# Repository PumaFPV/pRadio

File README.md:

# pRadio
PicoRadio, or PumaRadio, as you prefer...

A small VHF for paragliding. Configures via BLE with smartphone.
Since it has BLE connection to smartphone, could also be used as a remote to control XCtrack (move, zoom the map)
Mounts on the risers.
Aiming for 50g and ~10h of usage.

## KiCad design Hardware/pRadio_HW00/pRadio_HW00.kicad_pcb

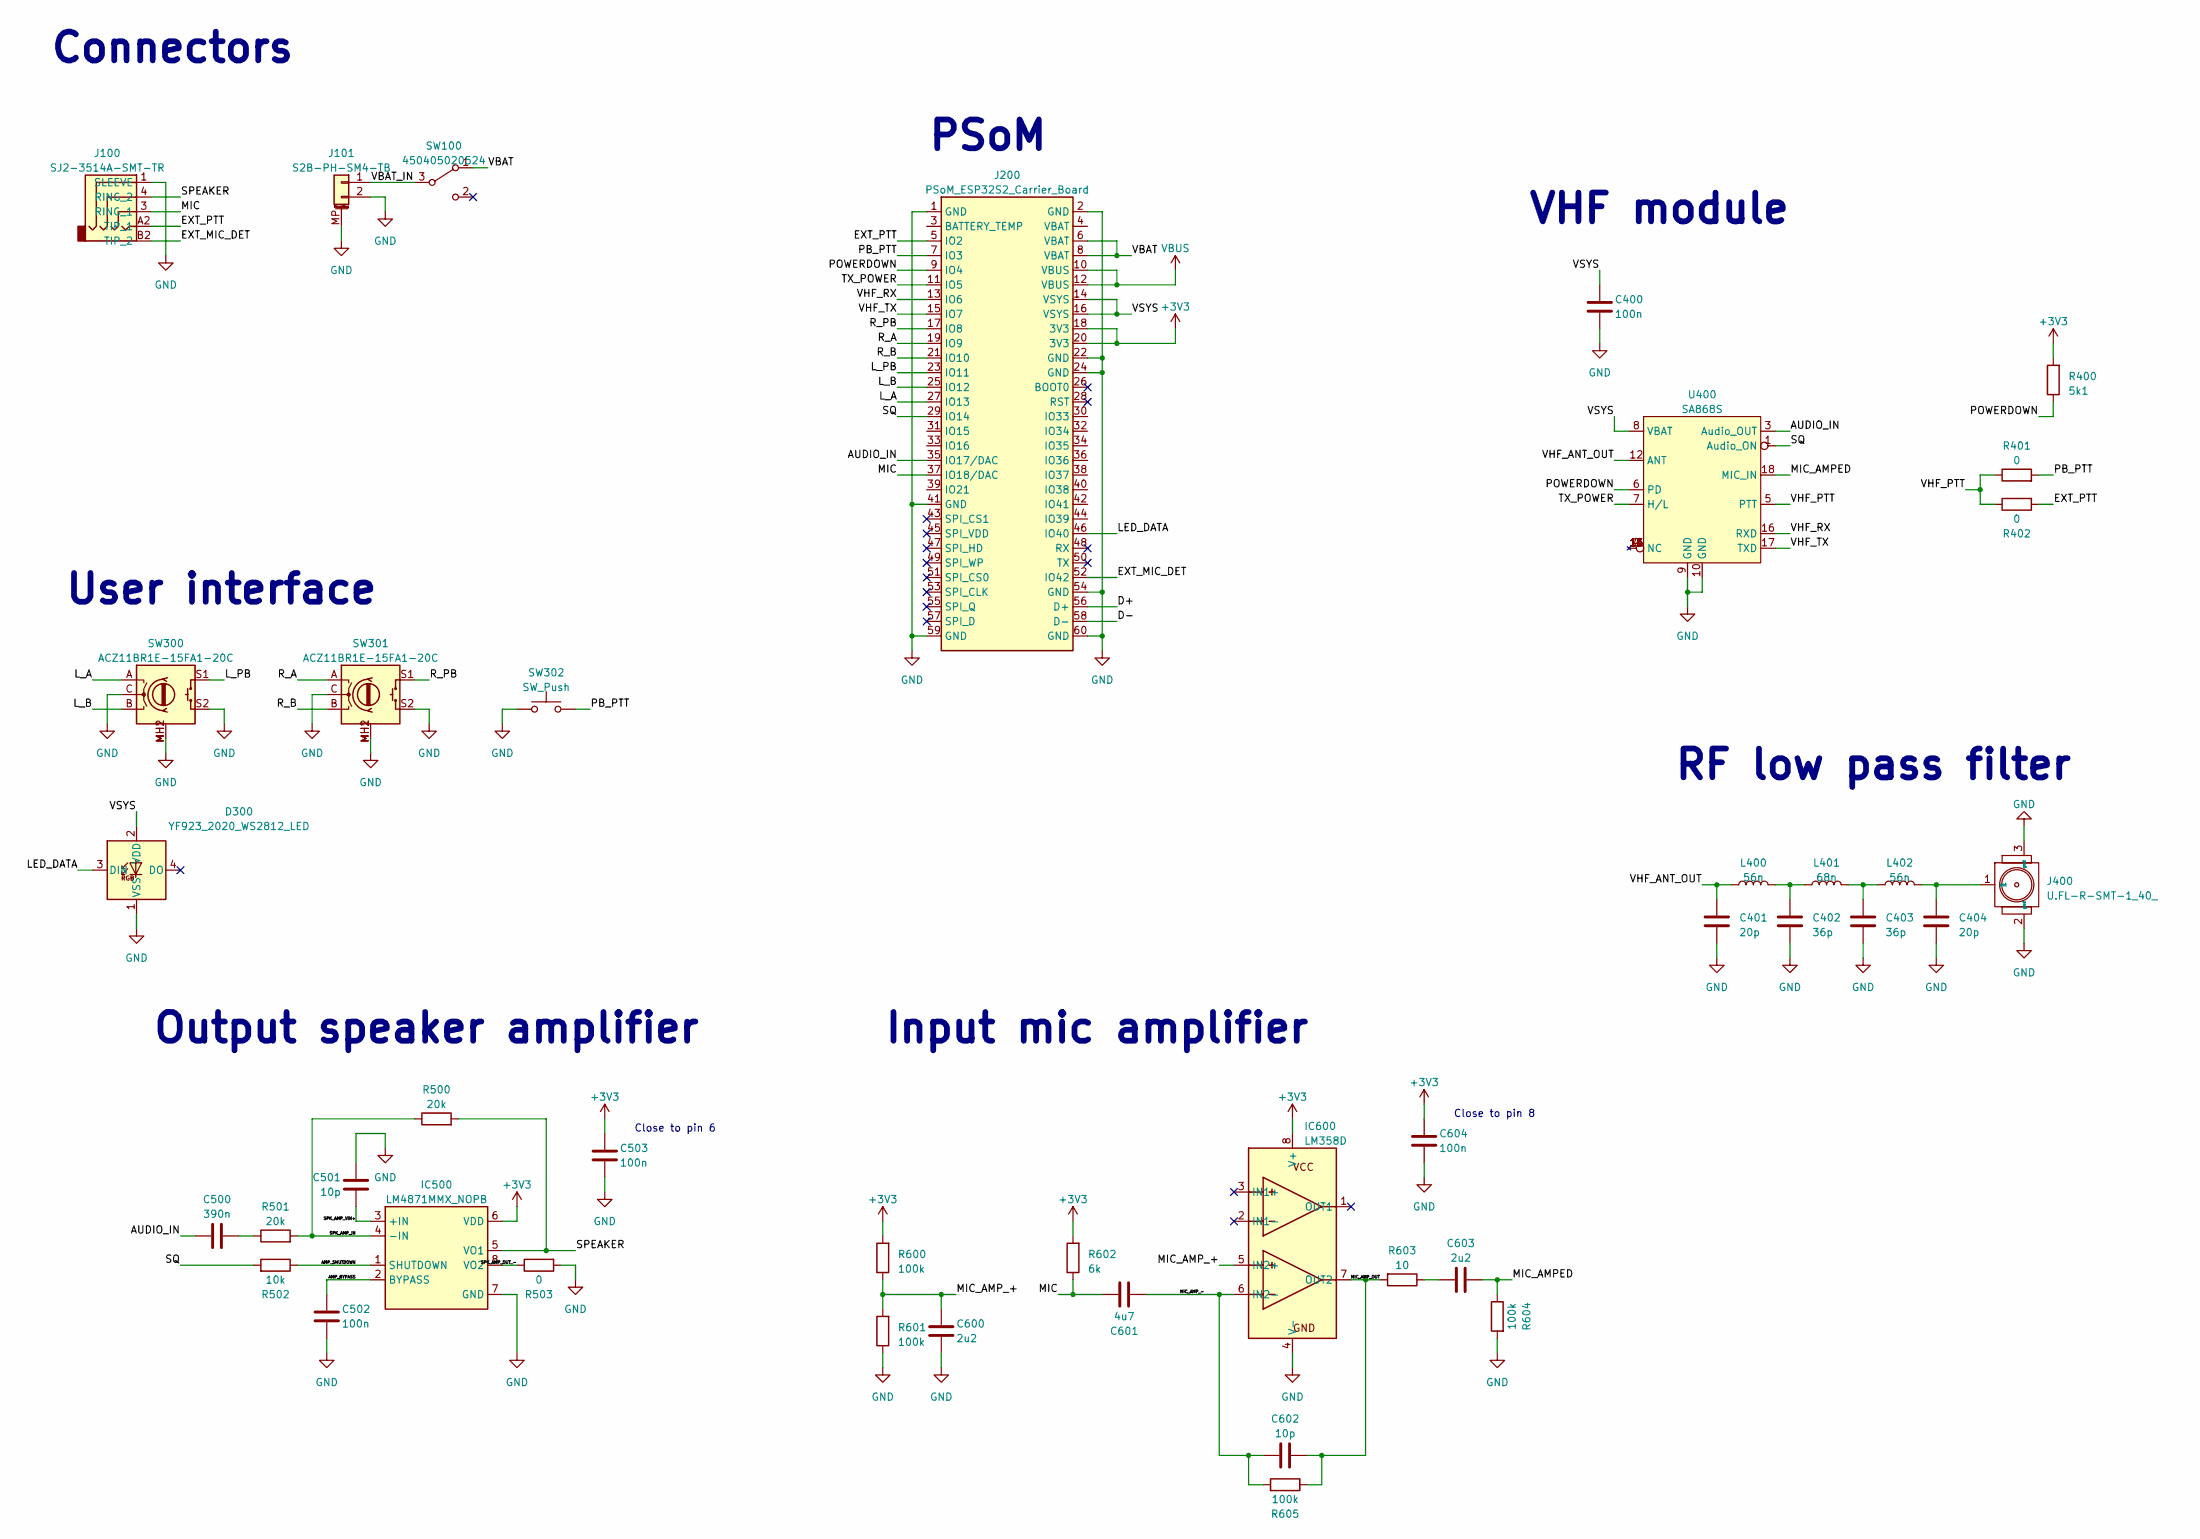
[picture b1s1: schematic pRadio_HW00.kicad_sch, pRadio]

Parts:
C400, C502, C503, C604: 100n; C_0402_1005Metric
C401, C404: 20p; C_0402_1005Metric
C402, C403: 36p; C_0402_1005Metric
C500: 390n; C_0603_1608Metric
C501, C602: 10p; C_0402_1005Metric
C600, C603: 2u2; C_0603_1608Metric
C601: 4u7; C_0603_1608Metric
D300: YF923_2020_WS2812_LED
IC500: LM4871MMX_NOPB; SOP65P490X110-8N; Mouser Part Number 926-LM4871MMX/NOPB
IC600: LM358D; SOIC127P600X175-8N; Mouser Part Number 511-LM358D
J100: SJ2-3514A-SMT-TR; SJ23514ASMTTR; Mouser Part Number 490-SJ2-3514A-SMT-TR
J101: S2B-PH-SM4-TB; JST_PH_S2B-PH-SM4-TB_1x02-1MP_P2.00mm_Horizontal
J200: PSoM_ESP32S2_Carrier_Board; PSoM_ESP32S2_00
J400: U.FL-R-SMT-1_40_; u.fl; Mouser Part Number 798-UFLRSMT140
L400, L402: 56n; L_0402_1005Metric
L401: 68n; L_0402_1005Metric
R400: 5k1; R_0201_0603Metric
R401, R402, R503: 0; R_0201_0603Metric
R500, R501: 20k; R_0201_0603Metric
R502: 10k; R_0201_0603Metric
R600, R601, R604, R605: 100k; R_0402_1005Metric
R602: 6k; R_0402_1005Metric
R603: 10; R_0402_1005Metric
SW100: 450405020524
SW300, SW301: ACZ11BR1E-15FA1-20C; ACZ11BR1E15FA120C
SW302: SW_Push; SW_Kailh_Choc_V1
U400: SA868S; RF818

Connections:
+3V3: C503.2, C604.2, IC500.6 (VDD), IC600.8 (V+), J200.18 (3V3), J200.20 (3V3), R400.2, R600.2, R602.2
/AMP_BYPASS: C502.2, IC500.2 (BYPASS)
/AMP_SHUTDOWN: IC500.1 (SHUTDOWN), R502.1
/AUDIO_IN: C500.1, J200.35 (IO17/DAC), U400.3 (Audio_OUT)
/D+: J200.56 (D+)
/D-: J200.58 (D-)
/EXT_MIC_DET: J100.B2 (TIP_2), J200.52 (IO42)
/EXT_PTT: J100.A2 (TIP_1), J200.5 (IO2), R402.2
/LED_DATA: D300.3 (DIN), J200.46 (IO40)
/L_A: J200.27 (IO13), SW300.A
/L_B: J200.25 (IO12), SW300.B
/L_PB: J200.23 (IO11), SW300.S1
/MIC: C601.1, J100.3 (RING_1), J200.37 (IO18/DAC), R602.1
/MIC_AMPED: C603.2, R604.1, U400.18 (MIC_IN)
/MIC_AMP_+: C600.2, IC600.5 (IN2+), R600.1, R601.2
/MIC_AMP_-: C601.2, C602.1, IC600.6 (IN2-), R605.2
/MIC_AMP_OUT: C602.2, IC600.7 (OUT2), R603.2, R605.1
/PB_PTT: J200.7 (IO3), R401.2, SW302.2
/POWERDOWN: J200.9 (IO4), R400.1, U400.6 (PD)
/R_A: J200.19 (IO9), SW301.A
/R_B: J200.21 (IO10), SW301.B
/R_PB: J200.17 (IO8), SW301.S1
/SPEAKER: IC500.5 (VO1), J100.4 (RING_2), R500.2
/SPK_AMP_IN: IC500.4 (-IN), R500.1, R501.2
/SPK_AMP_OUT_-: IC500.8 (VO2), R503.1
/SPK_AMP_VIN+: C501.1, IC500.3 (+IN)
/SQ: J200.29 (IO14), R502.2, U400.1 (Audio_ON)
/TX_POWER: J200.11 (IO5), U400.7 (H/L)
/VBAT: J200.6 (VBAT), J200.8 (VBAT), SW100.1 (A)
/VBAT_IN: J101.1, SW100.3 (B)
/VHF_ANT_OUT: C401.2, L400.1, U400.12 (ANT)
/VHF_PTT: R401.1, R402.1, U400.5 (PTT)
/VHF_RX: J200.13 (IO6), U400.16 (RXD)
/VHF_TX: J200.15 (IO7), U400.17 (TXD)
/VSYS: C400.2, D300.2 (VDD), J200.14 (VSYS), J200.16 (VSYS), U400.8 (VBAT)
GND: C400.1, C401.1, C402.1, C403.1, C404.1, C501.2, C502.1, C503.1, C600.1, C604.1, D300.1 (VSS), IC500.7 (GND), IC600.4 (V-), J100.1 (SLEEVE), J101.2, J101.MP (MountPin), J200.1 (GND), J200.2 (GND), J200.22 (GND), J200.24 (GND), J200.41 (GND), J200.54 (GND), J200.59 (GND), J200.60 (GND), J400.2 (gnd), J400.3 (gnd), R503.2, R601.1, R604.2, SW300.C, SW300.MH1, SW300.MH2, SW300.S2, SW301.C, SW301.MH1, SW301.MH2, SW301.S2, SW302.1, U400.9 (GND), U400.10 (GND)
unnamed: C402.2, L400.2, L401.1
unnamed: C403.2, L401.2, L402.1
unnamed: C500.2, R501.1
unnamed: C603.1, R603.1
unnamed: C404.2, J400.1 (ant), L402.2
VBUS: J200.10 (VBUS), J200.12 (VBUS)

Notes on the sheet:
User interface
Close to pin 6
PSoM
RF low pass filter
VHF module
Input mic amplifier
Output speaker amplifier
Close to pin 8
Connectors

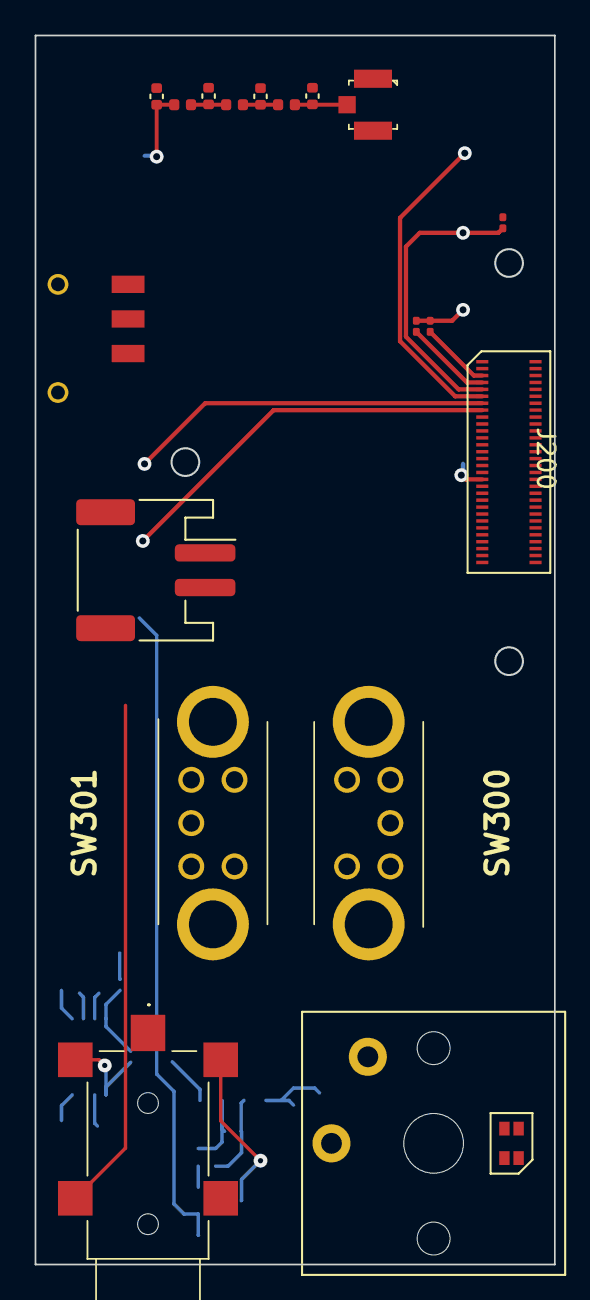
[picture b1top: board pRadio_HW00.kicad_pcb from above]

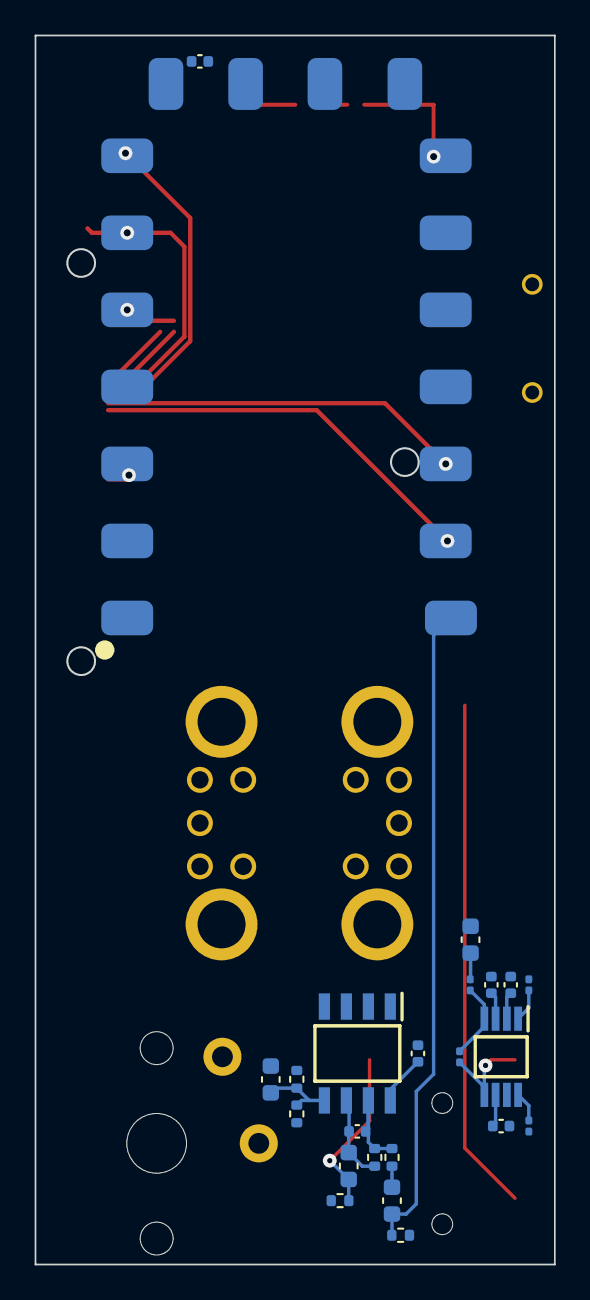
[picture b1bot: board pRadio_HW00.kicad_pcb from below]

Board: 4 copper layers, 30.0 x 71.0 mm, 42 parts (23 on the bottom side), 40 nets.

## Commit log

2024-02-20 Working on layout to see how compact it can get
2024-03-18 Created schematic
2024-03-19 Schematic done
2024-03-23 Working on routing
